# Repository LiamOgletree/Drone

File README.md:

Welcome! I'm designing a custom flight controller for drones. This Github page hosts all relevant files and technical details related to this effort, to include requisite project code and KiCAD schematic and PCB files.

The hardware design integrates STM32F446RE and ESP32-S3 microcontrollers, wireless and GPS (PA1616S) capabilities, and a custom IMU composed of an accelerometer and gyroscope (LSM6DSO32), barometer and temperature sensor (BMP388), and magnetometer (LIS2MDL). On the software side, I'm using STM32CubeIDE for my development environment; FreeRTOS for the OS; SPI for the LSM6DSO32, LIS2MDL, and BMP388 sensors; and DMA/UART for the PA1616S GPS receiver. Additionally, I use a Kalman Filter for state estimation &mdash; I would recommend <a href="https://github.com/rlabbe/Kalman-and-Bayesian-Filters-in-Python">this resource</a> for anyone interested in understanding Kalman Filters.

For the custom board design, I used <a href="https://www.kicad.org/">KiCAD</a> for schematic creation and the PCB layout and used <a href="https://jlcpcb.com/">JLCPCB</a> to manufacture physical boards. I'm sourcing drone components primarily from <a href="https://www.getfpv.com/">getfpv</a> (e.g., <a href="https://www.team-blacksheep.com/products/prod:sourceone_v5">this drone frame</a>) but there are many other FPV sites. Finally, for debugging purposes, I have a <a href="https://www.saleae.com/products/saleae-logic-pro-8">Saleae Logic Analyzer</a>.

See below for a functional overview of the code as it exists today:

Additionally, see below for layered 2D and rendered 3D images of the PCB design:

Please feel free to reach me at ogletreeliam@gmail.com with any questions or comments. Thank you!

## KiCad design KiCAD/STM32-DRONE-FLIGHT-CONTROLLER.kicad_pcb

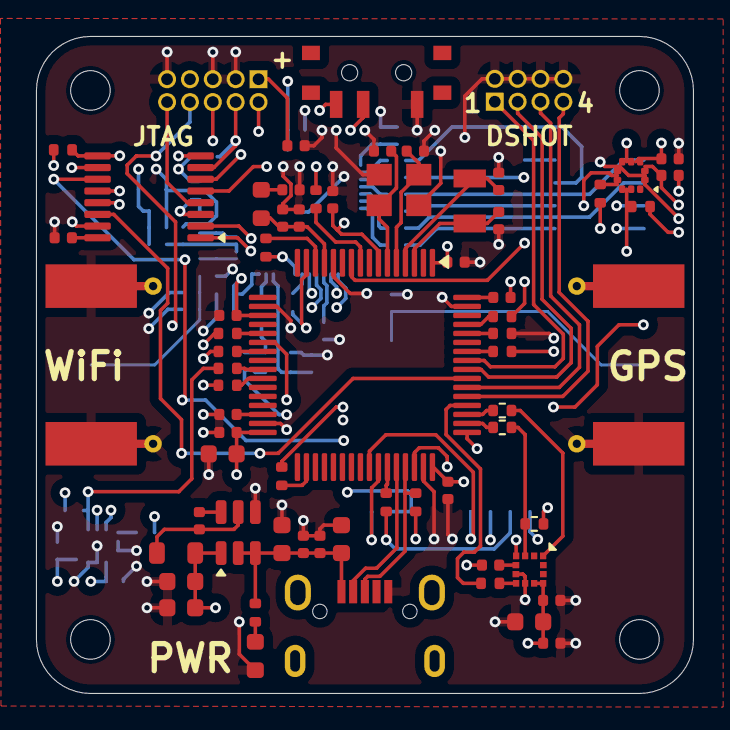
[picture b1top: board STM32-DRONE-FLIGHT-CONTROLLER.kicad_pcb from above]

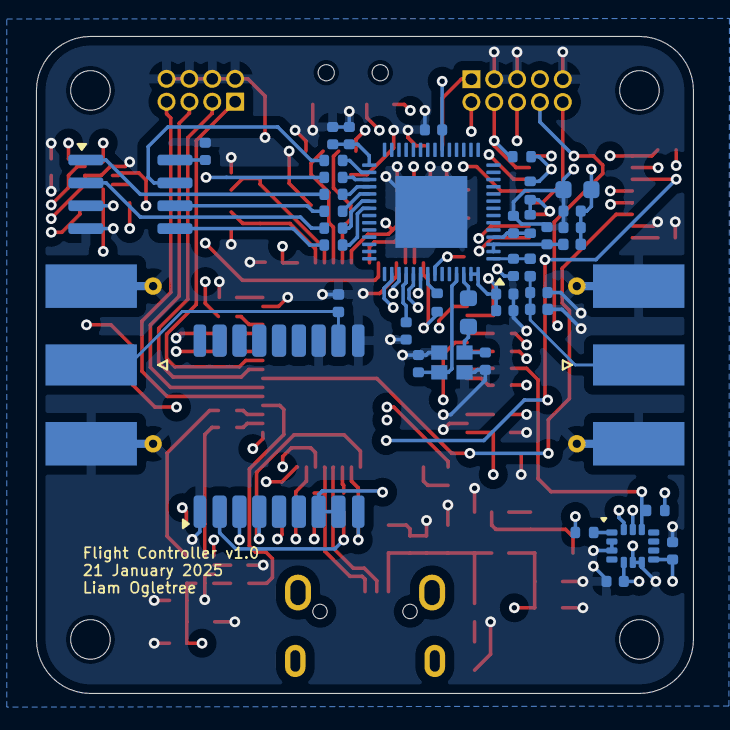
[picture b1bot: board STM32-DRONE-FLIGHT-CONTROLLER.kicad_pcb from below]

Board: 6 copper layers, 36.5 x 36.5 mm, 110 parts (42 on the bottom side), 88 nets.

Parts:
C1, C4, C8, C31, C44: 10uF; C_0603_1608Metric
C2, C21, C22, C23, C24, C35, C41, C45, C47, C48: 1uF; C_0402_1005Metric
C3, C5, C9, C10, C15, C16, C18, C19, C25, C26, C27, C28, C29, C30, C32, C37, C38, C39, C40, C42: 0.1uF; C_0402_1005Metric
C6, C7: 22uF; C_0603_1608Metric
C11, C12: 12.5pF; C_0402_1005Metric
C13, C14: 12pF; C_0402_1005Metric
C17: 2.2uF; C_0402_1005Metric
C20, C36: 10nF; C_0402_1005Metric
C33, C34: 10pF; C_0402_1005Metric
C43, C46: 1.2pF; C_0402_1005Metric
D1: Green; LED_0603_1608Metric
D2, D3: PESD0402-140; D_0402_1005Metric
FB1: 120R; L_0603_1608Metric
H1, H2, H3, H4: MountingHole; MountingHole_2.2mm_M2
J1: USB_B_Micro; USB_Micro-B_Wuerth_629105150521
J2: Conn_ARM_JTAG_SWD_10; PinHeader_2x05_P1.27mm_Vertical
J3: Conn_02x04_Odd_Even; PinHeader_2x04_P1.27mm_Vertical
J4, J5: Conn_Coaxial; SMA_Molex_73251-1153_EdgeMount_Horizontal
L1: 4.7uH; L_0805_2012Metric
L2: 24nH; L_0603_1608Metric
L3: 2nH; L_0402_1005Metric
L4: 2.4nH; L_0402_1005Metric
R1: 1k; R_0402_1005Metric
R2, R3, R4, R6, R7, R8, R9, R10, R18, R19, R20, R24, R25, R26, R27, R28, R29: 47R; R_0402_1005Metric
R5, R21, R22, R23, R31, R32: 10k; R_0402_1005Metric
R11, R12, R13, R14, R30: 33R; R_0402_1005Metric
R15: 1k5; R_0402_1005Metric
R16, R17: 100k; R_0402_1005Metric
SW1: SW_SPDT; SW_SPDT_PCM12
U1: AP63203WU; TSOT-23-6
U2: STM32F446RET6; LQFP-64_10x10mm_P0.5mm
U3: TMUX1574; TSSOP-16_4.4x5mm_P0.65mm
U4: ST_HLGA-10_2x2mm_P0.5mm_LayoutBorder3x2y
U5: LGA-12_2x2mm_P0.5mm
U6: LGA-14_3x2.5mm_P0.5mm_LayoutBorder3x4y
U7: MAX-M10S; ublox_MAX
U8: ESP32-S3; QFN-56-1EP_7x7mm_P0.4mm_EP4x4mm
U9: W25Q16JVSS; SOIC-8_3.9x4.9mm_P1.27mm
Y1: 32.768kHz; Crystal_SMD_3215-2Pin_3.2x1.5mm
Y2: 8MHz; Crystal_SMD_3225-4Pin_3.2x2.5mm
Y3: Crystal_GND24; Crystal_SMD_2016-4Pin_2.0x1.6mm

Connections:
+3.3V: C6.1, C7.1, C8.1, C9.1, C10.1, C15.1, C16.1, C19.1, C22.1, C23.1, C24.1, C26.2, C27.2, C28.2, C29.2, C30.2, C31.2, C32.2, C35.1, C36.1, C38.2, C39.2, C40.1, C41.1, C42.1, C44.1, C45.1, C48.1, FB1.1, J2.1 (VTref), L1.2, L3.2, R15.1, R16.1, R17.1, R21.1, R22.1, R23.1, R32.1, SW1.3 (C), U1.1 (FB), U2.1 (VBAT), U2.19 (VDD), U2.32 (VDD), U2.48 (VDD), U2.64 (VDD), U3.16 (VDD), U4.1 (VDDIO), U4.10 (VDD), U5.9 (VDD), U5.10 (VDDIO), U6.5 (VDDIO), U6.8 (VDD), U7.7 (VCC_IO), U7.8 (VCC), U8.20 (VDD3P3_RTC), U8.29 (VDD_SPI), U8.46 (VDD3P3_CPU), U8.55 (VDDA), U8.56 (VDDA), U9.8 (VCC)
+3.3VA: C20.1, C21.1, FB1.2, U2.13 (VDDA)
/Power/VBUS: C1.1, C2.1, C3.1, C4.1, J1.1 (VBUS), R1.1, U1.2 (EN), U1.3 (IN)
/STM32F446RET6/HSE_IN: C13.1, U2.5 (PH0), Y2.1
/STM32F446RET6/HSE_OUT: C14.1, U2.6 (PH1), Y2.3
/STM32F446RET6/LSE_IN: C11.1, U2.3 (PC14), Y1.1
/STM32F446RET6/LSE_OUT: C12.1, U2.4 (PC15), Y1.2
BMP388_CS: R14.1, R21.2, U4.6 (CS)
DSHOT1: J3.1, U2.57 (PB5)
DSHOT2: J3.3, U2.56 (PB4)
DSHOT3: J3.5, U2.54 (PD2)
DSHOT4: J3.7, U2.53 (PC12)
ESP32_MTCK: U3.6 (S2B), U8.44 (MTCK)
ESP32_MTDI: J2.8 (NC/TDI), U8.47 (MTDI)
ESP32_MTDO: U3.13 (S4B), U8.45 (MTDO)
ESP32_MTMS: U3.10 (S3B), U8.48 (MTMS)
ESP32_NRST: R31.1, R32.2, U3.3 (S1B)
GND: C1.2, C2.2, C3.2, C4.2, C6.2, C7.2, C8.2, C9.2, C10.2, C11.2, C12.2, C13.2, C14.2, C15.2, C16.2, C17.2, C18.2, C19.2, C20.2, C21.2, C22.2, C23.2, C24.2, C25.2, C26.1, C27.1, C28.1, C29.1, C30.1, C31.1, C32.1, C33.2, C34.2, C35.2, C36.2, C37.2, C38.1, C39.1, C40.2, C41.2, C42.2, C43.2, C44.2, C45.2, C46.2, C47.2, C48.2, D1.1 (K), D2.2 (A), D3.2 (A), J1.5 (GND), J2.3 (GND), J2.5 (GND), J2.9 (GNDDetect), J3.2, J3.4, J3.6, J3.8, J4.2 (Ext), J5.2 (Ext), R5.2, SW1.1 (A), U1.4 (GND), U2.12 (VSSA), U2.18 (VSS), U2.31 (VSS), U2.47 (VSS), U2.63 (VSS), U3.8 (GND), U3.15 (EN), U4.3 (GND), U4.8 (GND), U4.9 (GND), U5.6 (GND), U5.8 (GND), U6.2 (SDx), U6.3 (SCx), U6.6 (GND), U6.7 (GND), U7.1 (GND), U7.10 (GND), U7.12 (GND), U8.57 (GND), U9.4 (GND), Y2.2, Y2.4, Y3.2, Y3.4
LIS2MDL_CS: R8.2, R22.2, U5.3 (CS)
LSM6DSO32_CS: R3.1, R23.2, U6.12 (CS)
M10S_PPS: U2.41 (PA8), U7.4 (TIMEPULSE)
M10S_RESET: U2.42 (PA9), U7.9 (~RESET)
unnamed: C33.1, L2.1, Y3.1
unnamed: C37.1, L3.1, U8.2 (VDD3P3), U8.3 (VDD3P3)
unnamed: D1.2 (A), R1.2
unnamed: D2.1 (K), J4.1 (In), U7.11 (RF_IN)
unnamed: C46.1, D3.1 (K), J5.1 (In), L4.2
unnamed: SW1.2 (B), U3.1 (SEL)
unnamed: C5.1, U1.6 (BST)
unnamed: C5.2, L1.1, U1.5 (SW)
unnamed: R5.1, U2.60 (BOOT0)
unnamed: R11.2, U2.14 (PA0)
unnamed: R6.1, U2.21 (PA5)
unnamed: R7.1, U2.23 (PA7)
unnamed: R12.2, U2.43 (PA10)
unnamed: R8.1, U2.50 (PA15)
unnamed: R9.1, U2.26 (PB0)
unnamed: R13.2, U2.58 (PB6)
unnamed: R14.2, U2.61 (PB8)
unnamed: R10.1, U2.34 (PB13)
unnamed: R2.2, U2.9 (PC1)
unnamed: R3.2, U2.25 (PC5)
unnamed: R4.2, U2.51 (PC10)
unnamed: C17.1, U2.30 (VCAP_1)
unnamed: R18.2, U4.5 (SDO)
unnamed: C25.1, U5.5 (C1)
unnamed: R19.2, U5.7 (SDO)
unnamed: R20.2, U6.1 (SDO)
unnamed: C47.1, R31.2, U8.4 (CHIP_PU)
unnamed: C43.1, L4.1, U8.1 (LNA_IN)
unnamed: R27.2, U8.33 (SPICLK)
unnamed: R26.2, U8.32 (SPICS0)
unnamed: R29.2, U8.35 (SPID)
unnamed: R24.2, U8.30 (SPIHD)
unnamed: R28.2, U8.34 (SPIQ)
unnamed: R25.2, U8.31 (SPIWP)
unnamed: R30.2, U8.49 (U0TXD)
unnamed: C34.1, U8.53 (XTAL_N), Y3.3
unnamed: L2.2, U8.54 (XTAL_P)
SPI1_MISO: R20.1, U2.22 (PA6)
SPI1_MOSI: R7.2, U6.14 (SDI)
SPI1_SCK: R6.2, U6.13 (SCK)
SPI2_MISO: R18.1, U2.10 (PC2)
SPI2_MOSI: R2.1, U4.4 (SDI)
SPI2_SCK: R10.2, U4.2 (SCK)
SPI3_MISO: R19.1, U2.52 (PC11)
SPI3_MOSI: R9.2, U5.4 (SDI)
SPI3_SCK: R4.1, U5.1 (SCK)
SPICLK: R27.1, U9.6 (CLK)
SPICS0: R26.1, U9.1 (~CS)
SPID: R29.1, U9.5 (DI(IO0))
SPIHD: R24.1, U9.7 (IO3)
SPIQ: R28.1, U9.2 (DO(IO1))
SPIWP: R25.1, U9.3 (IO2)
STM32_NRST: C18.1, U2.7 (NRST), U3.2 (S1A)
STM32_SWCLK: U2.49 (PA14), U3.5 (S2A)
STM32_SWDIO: U2.46 (PA13), U3.11 (S3A)
STM32_SWO: U2.55 (PB3), U3.14 (S4A)
SWD_NRST: J2.10 (~RESET), U3.4 (D1)
SWD_SWCLK: J2.4 (SWCLK/TCK), R16.2, U3.7 (D2)
SWD_SWDIO: J2.2 (SWDIO/TMS), R17.2, U3.9 (D3)
SWD_SWO: J2.6 (SWO/TDO), U3.12 (D4)
UART4_MISO: R30.1, U2.15 (PA1)
UART4_MOSI: R11.1, U8.50 (U0RXD)
USART1_MISO: R12.1, U7.2 (TXD)
USART1_MOSI: R13.1, U7.3 (RXD)
USB_D+: J1.3 (D+), R15.2, U2.45 (PA12)
USB_D-: J1.2 (D-), U2.44 (PA11)

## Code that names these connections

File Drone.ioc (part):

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Mcu.Name=STM32F446R(C-E)Tx
Mcu.Package=LQFP64
Mcu.UserName=STM32F446RETx
PA0-WKUP.Mode=Asynchronous
PA0-WKUP.Signal=UART4_TX
PA1.Mode=Asynchronous
PA1.Signal=UART4_RX
PA10.Mode=Asynchronous
PA10.Signal=USART1_RX
PA11.Mode=Device_Only
PA11.Signal=USB_OTG_FS_DM
PA12.Mode=Device_Only
PA12.Signal=USB_OTG_FS_DP
PA13.GPIOParameters=GPIO_Label
PA13.GPIO_Label=TMS
PA13.Mode=Trace_Asynchronous_SW
PA13.Signal=SYS_JTMS-SWDIO
PA14.GPIOParameters=GPIO_Label
PA14.GPIO_Label=TCK
PA14.Mode=Trace_Asynchronous_SW
PA14.Signal=SYS_JTCK-SWCLK
PA2.GPIOParameters=GPIO_Label
PA2.GPIO_Label=USART_TX
PA2.Mode=Asynchronous
PA2.Signal=USART2_TX
PA3.GPIOParameters=GPIO_Label
PA3.GPIO_Label=USART_RX
PA3.Mode=Asynchronous
PA3.Signal=USART2_RX
PA5.Mode=Full_Duplex_Master
PA5.Signal=SPI1_SCK
PA6.Mode=Full_Duplex_Master
PA6.Signal=SPI1_MISO
PA7.Mode=Full_Duplex_Master
PA7.Signal=SPI1_MOSI
PA8.Signal=GPIO_Output
PB0.Mode=Full_Duplex_Master
PB0.Signal=SPI3_MOSI
PB10.GPIOParameters=PinState
PB10.PinState=GPIO_PIN_SET
PB10.Signal=GPIO_Output
PB13.Mode=Full_Duplex_Master
PB13.Signal=SPI2_SCK
PB3.Mode=Trace_Asynchronous_SW
PB3.Signal=SYS_JTDO-SWO
PB4.GPIOParameters=PinState
PB4.PinState=GPIO_PIN_SET
PB4.Signal=GPIO_Output
PB6.Mode=Asynchronous
PB6.Signal=USART1_TX
PC1.Mode=Full_Duplex_Master
PC1.Signal=SPI2_MOSI
PC10.Mode=Full_Duplex_Master
PC10.Signal=SPI3_SCK
PC11.Mode=Full_Duplex_Master
PC11.Signal=SPI3_MISO
PC13.GPIOParameters=GPIO_Label,GPIO_ModeDefaultEXTI
PC13.GPIO_Label=B1 [Blue PushButton]
PC13.GPIO_ModeDefaultEXTI=GPIO_MODE_IT_FALLING
PC13.Signal=GPXTI13
PC14-OSC32_IN.Mode=LSE-External-Oscillator
PC14-OSC32_IN.Signal=RCC_OSC32_IN
PC15-OSC32_OUT.Mode=LSE-External-Oscillator
PC15-OSC32_OUT.Signal=RCC_OSC32_OUT
PC2.Mode=Full_Duplex_Master
PC2.Signal=SPI2_MISO
PH0-OSC_IN.Mode=HSE-External-Oscillator
PH0-OSC_IN.Signal=RCC_OSC_IN
PH1-OSC_OUT.Mode=HSE-External-Oscillator
PH1-OSC_OUT.Signal=RCC_OSC_OUT
RCC.HSE_VALUE=8000000
RCC.SYSCLKFreq_VALUE=84000000
RCC.SYSCLKSource=RCC_SYSCLKSOURCE_PLLCLK
board=NUCLEO-F446RE
boardIOC=true

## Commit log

2024-09-09 fix spacing
    spacing fixed
2024-09-09 actual spacing fix
2024-09-14 Refactor BMP388
2024-09-26 Refinement
    Refined existing code, i.e., added error checking, reformatted for consistency, etc.
2024-09-30 BMP388 bug fix
    added volatile temperature variable for compensate_pressure function to use
2024-10-05 refinements and race conditions fixes
    added mutexes for shared resources, updated Kalman Filter, and began work on state machine task
2024-10-15 code refinements and gitignore first attempt
2024-10-15 testing gitignore
2024-10-16 Attempt 2 to remove gitignore files
2024-10-16 Removing middlewares
2024-10-26 rework LSM6DSO32 and dynamically get timestamps
2025-01-21 Renaming files and variables for readability
2025-01-21 removing extraneous document
2025-01-21 Adding KiCAD design files
